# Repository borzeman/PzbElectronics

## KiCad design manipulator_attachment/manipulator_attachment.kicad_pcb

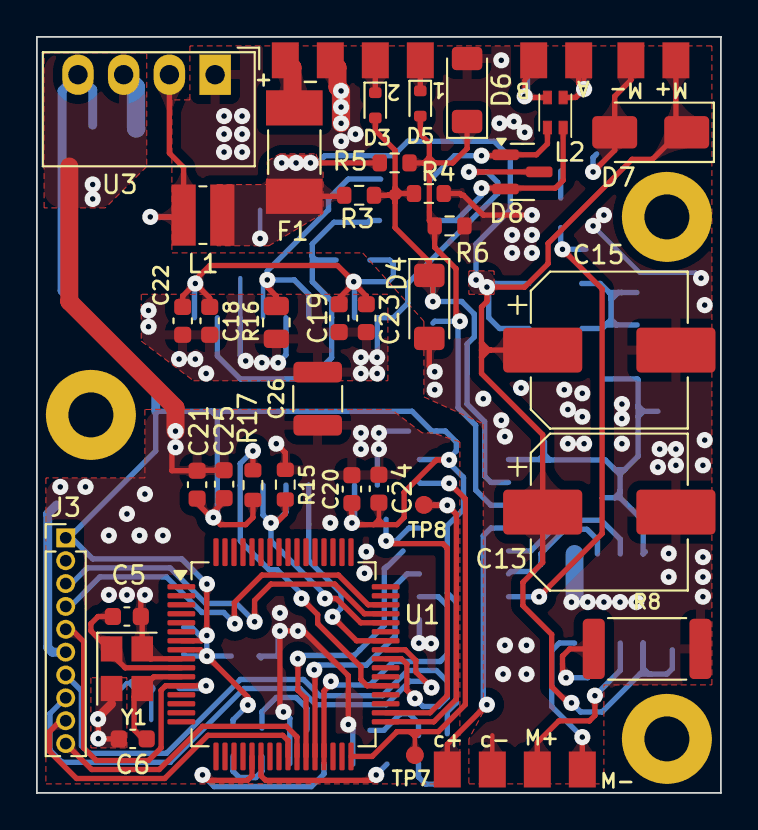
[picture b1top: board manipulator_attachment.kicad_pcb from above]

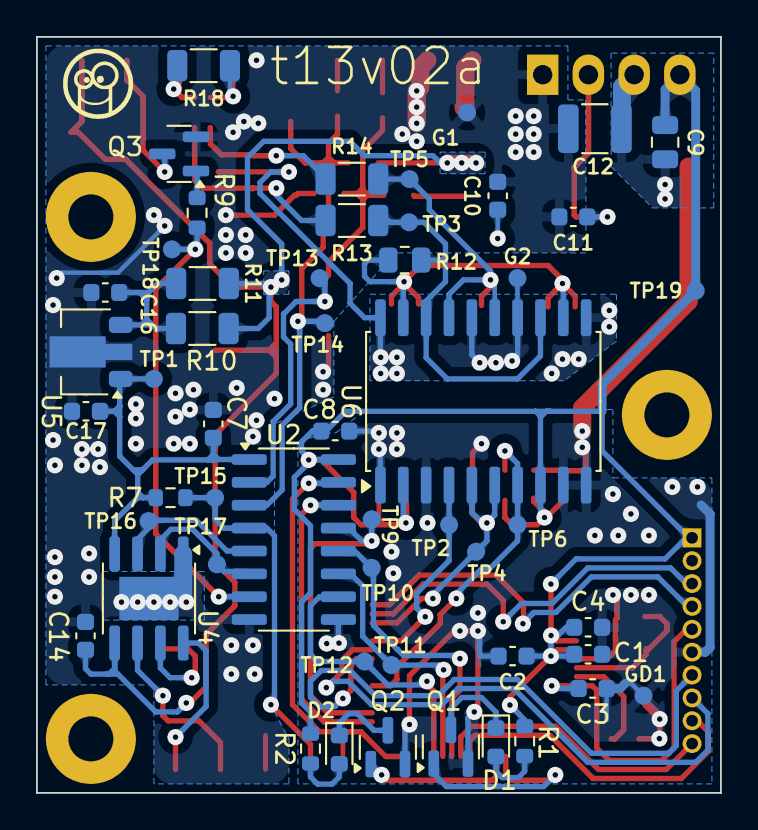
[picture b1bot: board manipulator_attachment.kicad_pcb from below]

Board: 2 copper layers, 38.0 x 42.0 mm, 95 parts (52 on the bottom side), 53 nets.

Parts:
C1, C3, C4, C7, C8, C17, C19, C20, C22, C25: 0,1uF 100V 0603; C_0603_1608Metric
C2, C10, C11: 4,7uF 50V 0603; C_0603_1608Metric
C5, C6: 20pF 50V 0603; C_0603_1608Metric
C9: 10uF 50V 0805; C_0805_2012Metric
C12, C26: 270 pf X7R 1206 2000v 202R18W271KW4E; C_1210_3225Metric
C13: 100uF 50V (SMD 8х10); CP_Elec_8x10.5
C14: 0.22uF 50V 0603; C_0603_1608Metric
C15: 47uF 63V SMD; CP_Elec_8x10.5
C16: 0,33uF 50V 0603; C_0603_1608Metric
C18, C21: 10uF 16V 0603; C_0603_1608Metric
C23, C24: 10nF 50V 0603; C_0603_1608Metric
D1, D2: TO-1608BC-BF; LED_0603_1608Metric
D3, D5: 1PS79SB30; D_SOD-523
D4, D6: BZV55B3V3; D_MiniMELF
D7: SS16; D_SMA
D8: PSM712; SOT-23
F1: 045201.5MRL; Fuse_Littelfuse-NANO2-451_453
G1, G2: TestPoint; TestPoint_Pad_D1.0mm
GD1: TestPoint; TestPoint_Pad_D1.0mm
H1, H2, H3: MountingHole; MountingHole_2.5mm_Pad
J1: RS485; PAD_1.5x2mm_2
J3: DS1031-01-1х10 (PLL - 1x10) (prog); PinHeader_1x10_P1.27mm_Vertical
J4: Magnit; PAD_1.5x2mm_2
J5: Control; PAD_1.5x2mm_4
J6: IN_VCC_DO; PAD_1.5x2mm_4
L1: 6,8uH 0,95A (SM3521-6R8MT); L_Wuerth_MAPI-3020
L2: DLW21SN900SQ2L; L_CommonModeChoke_Coilcraft_0805USB
Q1, Q2: DTC114ECA (SOT-23); SOT-23
Q3: FDN5630; SOT-23
R1, R2: 0603-150 Ом±5%-0,0625 Вт; R_0603_1608Metric
R3, R5: 24k 0603; R_0603_1608Metric
R4, R6: 3.6k 0603; R_0603_1608Metric
R7: 0603 10 кОм; R_0603_1608Metric
R8: 0R51 2512; R_2512_6332Metric
R9: 101 0603; R_0603_1608Metric
R10: 1206-620 Ом±5%-0,25 Вт; R_1206_3216Metric
R11: 1206 opt; R_1206_3216Metric
R12, R16: 0805-560 Ом±5%-0,125 Вт; R_0805_2012Metric
R13, R14: 1206-100 Ом±5%-0,25 Вт; R_1206_3216Metric
R15, R17: 0603-10 кОм±5%-0,0625 Вт; R_0603_1608Metric
R18: 1206-120 Ом±5%-0,25 Вт; R_1206_3216Metric
TP1, TP2, TP3, TP4, TP5, TP6, TP7, TP8, TP9, TP10, TP11, TP12, TP13, TP14, TP15, TP16, TP17, TP18, TP19: TestPoint; TestPoint_Pad_D1.0mm
U1: STM32G070RBTx (LQFP-64); LQFP-64_10x10mm_P0.5mm
U2: π163M3x; SOIC-16_3.9x9.9mm_P1.27mm
U3: AM1SS-2403SJZ; Converter_DCDC_Murata_MEE1SxxxxSC_THT
U4: A4950E; SOIC-8-1EP_3.9x4.9mm_P1.27mm_EP2.41x3.3mm
U5: L78L33_SOT89; SOT-89-3
U6: ADM2587E (SOIC-20); SOIC-20W_7.5x12.8mm_P1.27mm
Y1: Crystal_3225 8MHz; Crystal_SMD_3225-4Pin_3.2x2.5mm

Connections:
+3.3VA: C7.2, C17.1, R7.1, TP1.1, U2.1 (VDD1), U4.4 (VREF), U5.1 (OUT)
+3V3: C1.1, C2.1, C4.1, C8.2, C9.1, C20.1, C21.2, C24.1, C25.2, J3.1, R1.2, R2.2, R17.1, TP19.1, U1.7 (VREF+), U1.8 (VDD), U2.16 (VDD2), U3.4 (OUT+), U6.2 (VCC), U6.8 (VCC)
+24V: C10.1, C13.1, C14.2, C15.1, D7.1 (K), F1.1, J4.2, L1.1, R3.1, R5.2, R10.2, R11.2, U4.5 (VBB)
/A: J1.2, L2.2, R18.2
/B: J1.1, L2.3, R18.1
/Catch: TP16.1, U2.5 (VOD), U4.3 (IN1)
/Catch_contr: TP10.1, U1.27 (PB0), U2.12 (VID)
/Contact+: J5.1, R7.2, TP15.1, U2.4 (VIC)
/Contakt_signal_contr: TP9.1, U1.34 (PB14), U2.13 (VOC)
/DE_USART_1: R15.1, TP4.1, U1.44 (PA12/PA10), U6.5 (~RE), U6.6 (DE)
/GPIO1: J3.9, U1.25 (PC4)
/GPIO2: J3.10, U1.26 (PC5)
/Magnit-: D7.2 (A), J4.1, Q3.3 (D)
/Motor+: J5.3, U4.6 (OUT1)
/Motor-: J5.4, U4.8 (OUT2)
/NRST: C3.2, J3.5, U1.12 (NRST)
/ON/OFF magnet: R9.1, TP18.1, U2.7 (VOF)
/ON/OFF magnet_contr: TP12.1, U1.29 (PB2), U2.10 (VIF)
/OSC_IN: C5.1, U1.10 (PF0), Y1.1
/OSC_OUT: C6.1, U1.11 (PF1), Y1.3
/RX_USART_1: TP2.1, U1.42 (PA10/NC), U6.4 (RxD)
/SWCLK: J3.4, U1.46 (PA14)
/SWDIO: J3.3, U1.45 (PA13)
/TX_USART_1: R17.2, TP6.1, U1.37 (PA9/NC), U6.7 (TxD)
/UART_RX: J3.8, U1.41 (PD9)
/UART_TX: J3.7, U1.40 (PD8)
/Uncatch: TP17.1, U2.6 (VOE), U4.2 (IN2)
/Uncatch_contr: TP11.1, U1.28 (PB1), U2.11 (VIE)
/gripper_signal: D5.2 (A), D6.1 (K), R5.1, R6.1, TP14.1, U2.3 (VIB)
/gripper_signal_contr: TP8.1, U1.33 (PB13), U2.14 (VOB)
/magnit_signal: D3.2 (A), D4.1 (K), R3.2, R4.1, TP13.1, U2.2 (VIA)
/magnit_signal_contr: TP7.1, U1.32 (PB12), U2.15 (VOA)
GND: C7.1, C10.2, C11.2, C12.1, C13.2, C14.1, C15.2, C16.2, C17.2, D4.2 (A), D6.2 (A), G1.1, J5.2, J6.2, Q3.2 (S), R4.2, R6.2, R8.2, U2.8 (GND1), U3.1 (IN-), U4.1 (GND), U4.9 (PAD), U5.2 (GND)
GND2: C18.2, C19.1, C22.2, C23.1, C26.2, D8.3 (Com), G2.1, R16.1, U6.11 (GND2), U6.14 (GND2), U6.16 (GND2), U6.20 (GND2)
GNDD: C1.2, C2.2, C3.1, C4.2, C5.2, C6.2, C8.1, C9.2, C12.2, C20.2, C21.1, C24.2, C25.1, C26.1, GD1.1, J3.6, Q1.2 (E), Q2.2 (E), R15.2, U1.9 (VSS), U2.9 (GND2), U3.3 (OUT-), U6.1 (GND1), U6.3 (GND1), U6.9 (GND1), U6.10 (GND1), Y1.2, Y1.4
unnamed: D1.2 (A), R1.1
unnamed: D1.1 (K), Q1.3 (C)
unnamed: D2.2 (A), R2.1
unnamed: D2.1 (K), Q2.3 (C)
unnamed: D3.1 (K), J6.3
unnamed: D5.1 (K), J6.4
unnamed: D8.1 (A1), L2.4, R14.1
unnamed: D8.2 (A2), L2.1, R13.2
unnamed: F1.2, J6.1
unnamed: Q1.1 (B), U1.21 (PA4)
unnamed: Q2.1 (B), U1.22 (PA5)
unnamed: Q3.1 (G), R9.2
unnamed: C11.1, L1.2, U3.2 (IN+)
unnamed: R8.1, U4.7 (LSS)
unnamed: C16.1, R10.1, R11.1, U5.3 (IN)
unnamed: R12.2, R13.1, TP3.1, U6.13 (Y), U6.18 (A)
unnamed: R14.2, R16.2, TP5.1, U6.15 (Z), U6.17 (B)
unnamed: C18.1, C19.2, C22.1, C23.2, R12.1, U6.12 (Visoout), U6.19 (Visoin)
